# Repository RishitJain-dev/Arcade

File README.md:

# Arcade
A custom console similar to the Nintendo Game&amp;Watch, with a large colorful screen, d-pad and A and B button. It also includes a USB-C connector and SD card slot. 

Using SK8612-MINI-E LEDs to provide as a visual indicator of when a button is pressed

It uses a ESP32 chip to power it and recieves power directly from a LiPo battery.

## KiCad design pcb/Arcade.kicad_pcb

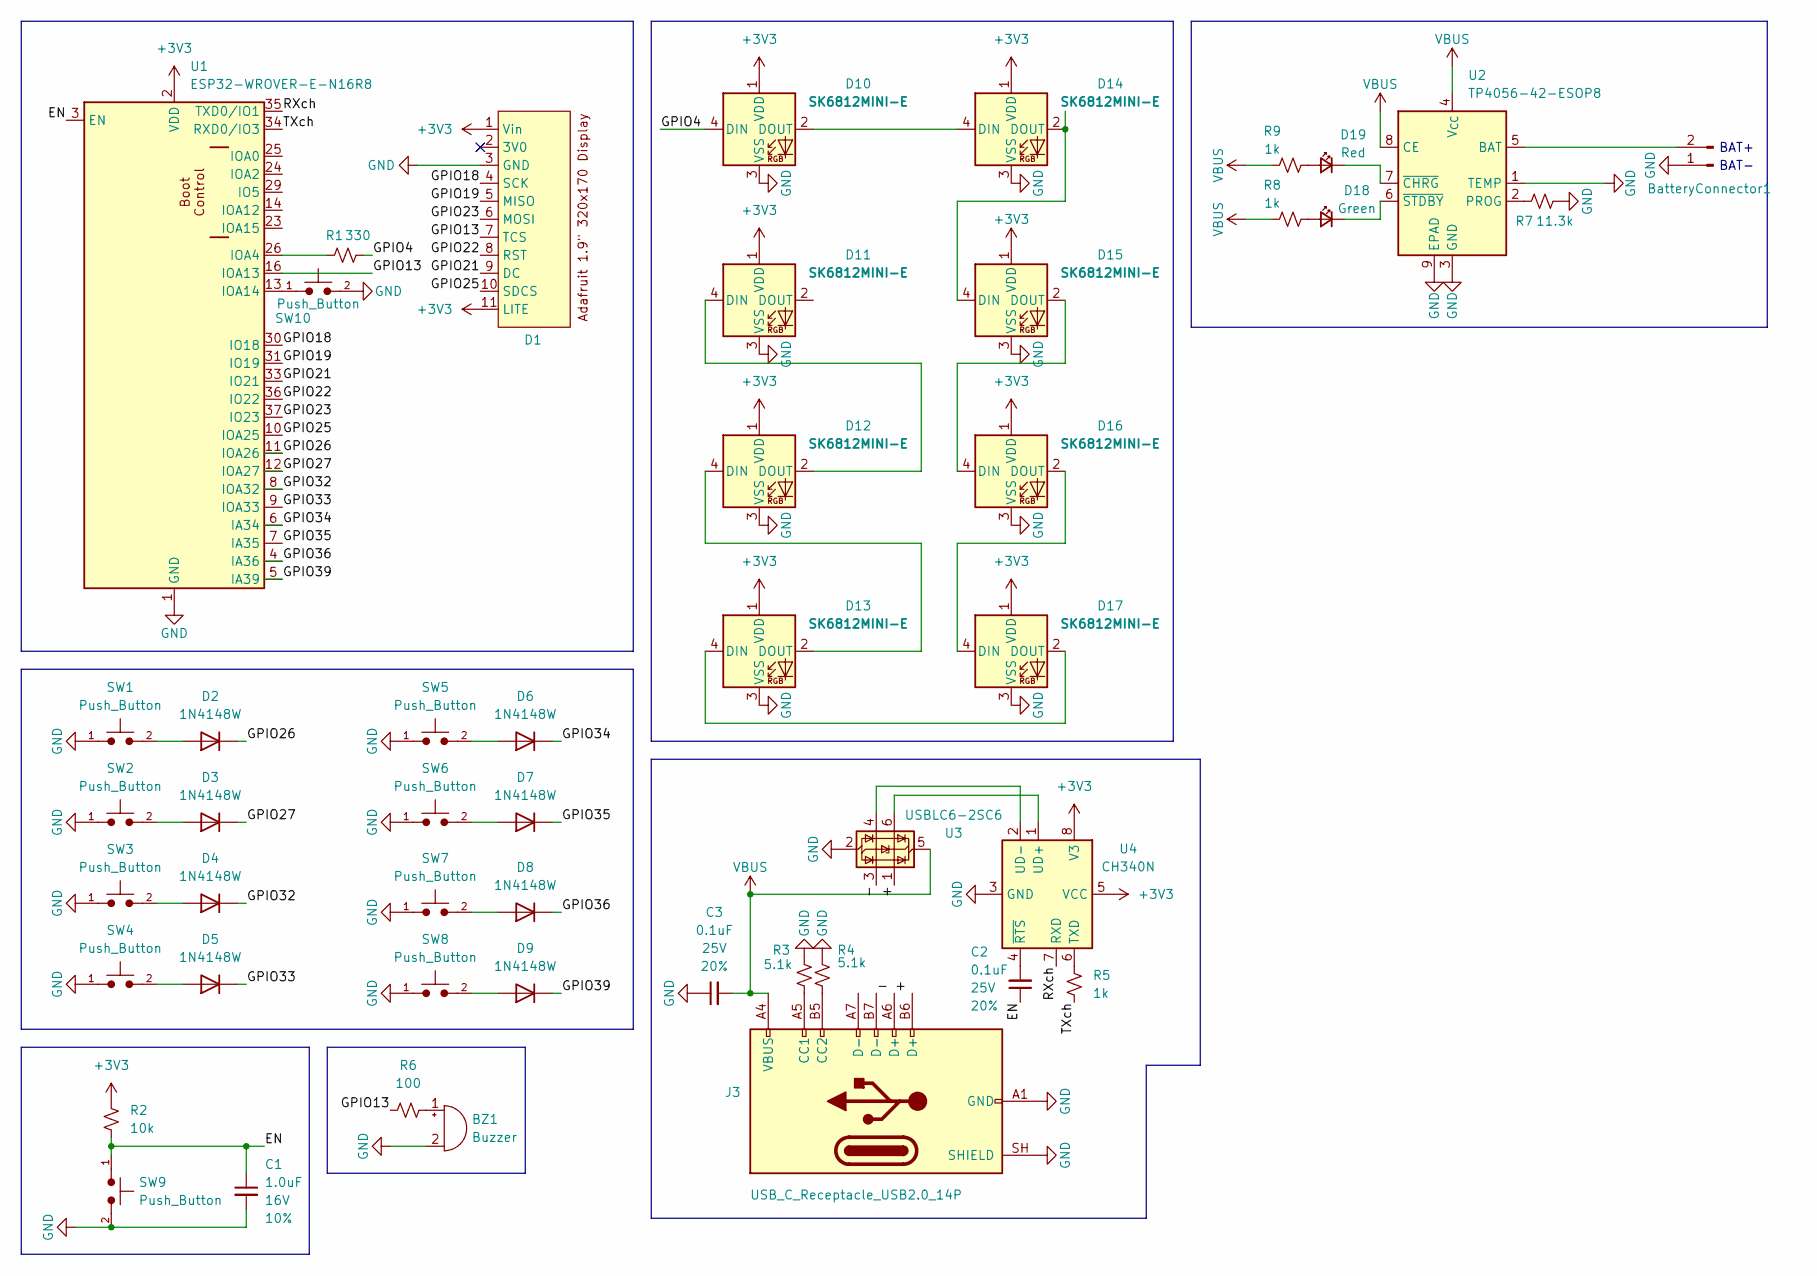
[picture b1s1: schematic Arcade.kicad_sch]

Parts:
BZ1: Buzzer; Buzzer_12x9.5RM7.6
BatteryConnector1: BAT-; JST_EH_B2B-EH-A_1x02_P2.50mm_Vertical
C1: 1.0uF; C_0603_1608Metric; Voltage 16V; Tolerance 10%
C2, C3: 0.1uF; C_0603_1608Metric; Voltage 25V; Tolerance 20%
D1: Adafruit 1.9 320x170 Colour IPS TFT Display (ST7789)
D2, D3, D4, D5, D6, D7, D8, D9: 1N4148W; D_SOD-123
D10, D11, D12, D13, D14, D15, D16, D17: SK6812MINI-E; LED_SK6812MINI-E_3.2x2.8mm_P1.5mm_ReverseMount
D18: Green; LED_0603_1608Metric_Green
D19: Red; LED_0603_1608Metric_Red
J3: USB_C_Receptacle_USB2.0_14P; USB_C_Receptacle_HRO_TYPE-C-31-M-12
R1: 330; R_0603_1608Metric
R2: 10k; R_0603_1608Metric
R3, R4: 5.1k; R_0603_1608Metric
R5, R8, R9: 1k; R_0603_1608Metric
R6: 100; R_0603_1608Metric
R7: 11.3k; R_0603_1608Metric
SW1, SW2, SW3, SW4, SW5, SW6, SW7, SW8, SW9, SW10: Push_Button; SW_PUSH_6mm
U1: ESP32-WROVER-E-N16R8; ESP32-WROVER-E-IE
U2: TP4056-42-ESOP8; SOIC-8-1EP_3.9x4.9mm_P1.27mm_EP2.41x3.3mm_ThermalVias
U3: USBLC6-2SC6; SOT-23-6
U4: CH340N; JEITA_SOIC-8_3.9x4.9mm_P1.27mm

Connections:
+3V3: D1.1 (Vin), D1.11 (LITE), D10.1 (VDD), D11.1 (VDD), D12.1 (VDD), D13.1 (VDD), D14.1 (VDD), D15.1 (VDD), D16.1 (VDD), D17.1 (VDD), R2.2, U1.2 (VDD), U4.5 (VCC), U4.8 (V3)
/+: J3.A6 (D+), U3.1 (I/O1)
/-: J3.B7 (D-), U3.3 (I/O2)
/EN: C1.1, C2.1, R2.1, SW9.1, U1.3 (EN)
/GPIO4: D10.4 (DIN), R1.2
/GPIO13: D1.7 (TCS), R6.1, U1.16 (IOA13)
/GPIO18: D1.4 (SCK), U1.30 (IO18)
/GPIO19: D1.5 (MISO), U1.31 (IO19)
/GPIO21: D1.9 (DC), U1.33 (IO21)
/GPIO22: D1.8 (RST), U1.36 (IO22)
/GPIO23: D1.6 (MOSI), U1.37 (IO23)
/GPIO25: D1.10 (SDCS), U1.10 (IOA25)
/GPIO26: D2.1 (K), U1.11 (IOA26)
/GPIO27: D3.1 (K), U1.12 (IOA27)
/GPIO32: D4.1 (K), U1.8 (IOA32)
/GPIO33: D5.1 (K), U1.9 (IOA33)
/GPIO34: D6.1 (K), U1.6 (IA34)
/GPIO35: D7.1 (K), U1.7 (IA35)
/GPIO36: D8.1 (K), U1.4 (IA36)
/GPIO39: D9.1 (K), U1.5 (IA39)
/RXch: U1.35 (TXD0/IO1), U4.7 (RXD)
/TXch: R5.1, U1.34 (RXD0/IO3)
GND: BZ1.2 (-), BatteryConnector1.1, C1.2, C3.1, D1.3 (GND), D10.3 (VSS), D11.3 (VSS), D12.3 (VSS), D13.3 (VSS), D14.3 (VSS), D15.3 (VSS), D16.3 (VSS), D17.3 (VSS), J3.A1 (GND), J3.A12 (GND), J3.B1 (GND), J3.B12 (GND), J3.SH (SHIELD), R3.2, R4.2, R7.2, SW1.1, SW2.1, SW3.1, SW4.1, SW5.1, SW6.1, SW7.1, SW8.1, SW9.2, SW10.2, U1.1 (GND), U1.15 (GND), U1.38 (GND), U1.39.1 (GND), U1.39.2 (GND), U1.39.3 (GND), U1.39.4 (GND), U1.39.5 (GND), U1.39.6 (GND), U1.39.7 (GND), U1.39.8 (GND), U1.39.9 (GND), U2.1 (TEMP), U2.3 (GND), U2.9 (EPAD), U3.2 (GND), U4.3 (GND)
unnamed: BZ1.1 (+), R6.2
unnamed: BatteryConnector1.2, U2.5 (BAT)
unnamed: D2.2 (A), SW1.2
unnamed: D3.2 (A), SW2.2
unnamed: D4.2 (A), SW3.2
unnamed: D5.2 (A), SW4.2
unnamed: D6.2 (A), SW5.2
unnamed: D7.2 (A), SW6.2
unnamed: D8.2 (A), SW7.2
unnamed: D9.2 (A), SW8.2
unnamed: D10.2 (DOUT), D14.4 (DIN)
unnamed: D11.4 (DIN), D12.2 (DOUT)
unnamed: D12.4 (DIN), D13.2 (DOUT)
unnamed: D13.4 (DIN), D17.2 (DOUT)
unnamed: D14.2 (DOUT), D15.4 (DIN)
unnamed: D15.2 (DOUT), D16.4 (DIN)
unnamed: D16.2 (DOUT), D17.4 (DIN)
unnamed: D18.2 (A), R8.2
unnamed: D18.1 (K), U2.6 (~STDBY)
unnamed: D19.2 (A), R9.2
unnamed: D19.1 (K), U2.7 (~CHRG)
unnamed: J3.A5 (CC1), R3.1
unnamed: J3.B5 (CC2), R4.1
unnamed: R1.1, U1.26 (IOA4)
unnamed: SW10.1, U1.13 (IOA14)
unnamed: R7.1, U2.2 (PROG)
unnamed: R5.2, U4.6 (TXD)
unnamed: U3.6 (I/O1), U4.1 (UD+)
unnamed: U3.4 (I/O2), U4.2 (UD-)
unnamed: C2.2, U4.4 (~RTS)
VBUS: C3.2, J3.A4 (VBUS), J3.A9 (VBUS), J3.B4 (VBUS), J3.B9 (VBUS), R8.1, R9.1, U2.4 (V_{CC}), U2.8 (CE), U3.5 (VBUS)

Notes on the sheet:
BAT+
BAT-

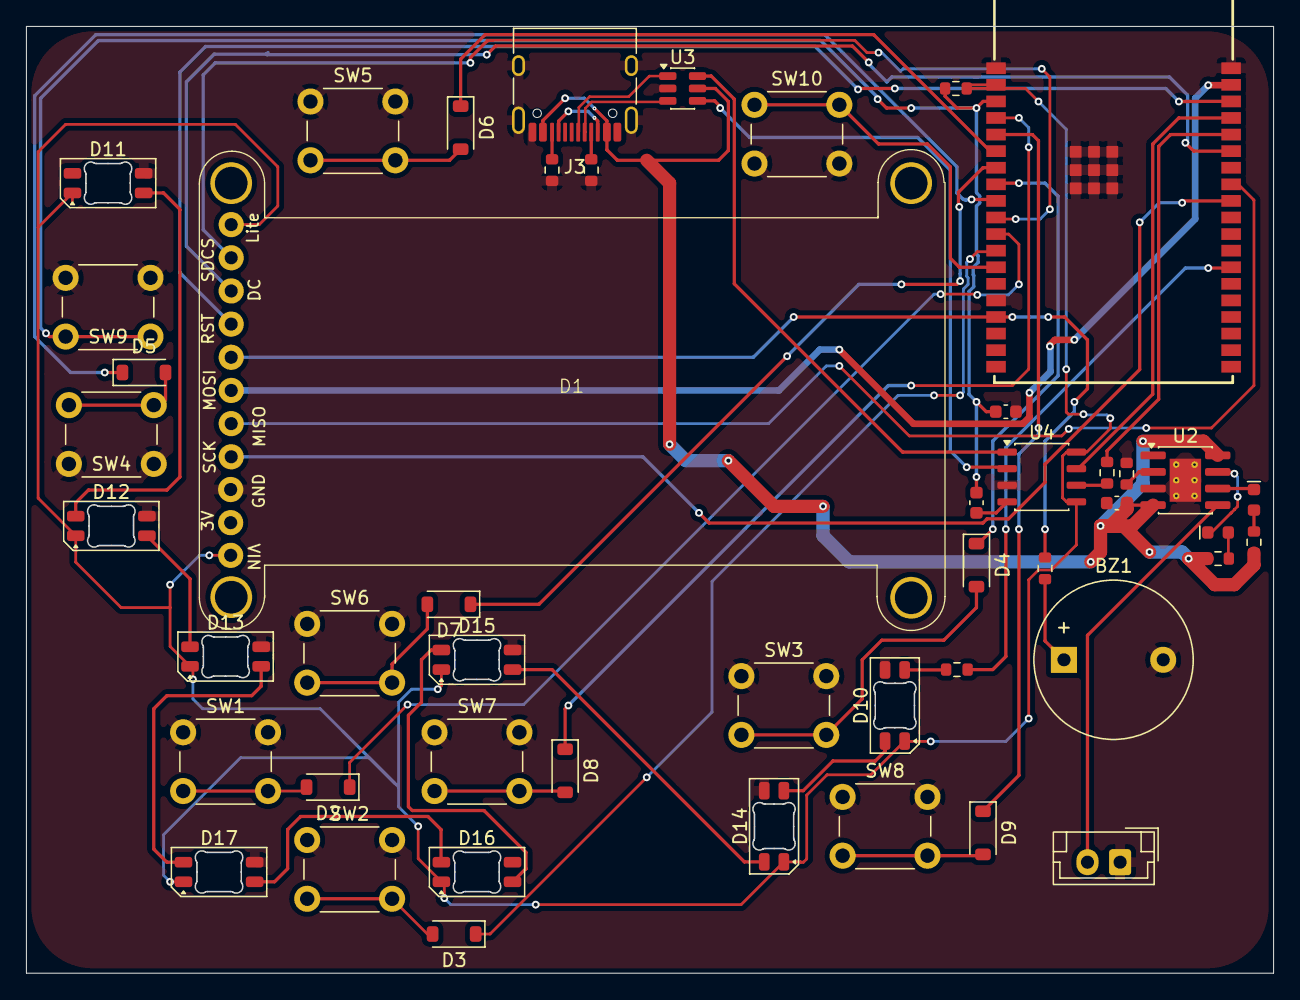
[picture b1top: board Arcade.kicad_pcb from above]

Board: 2 copper layers, 95.5 x 72.5 mm, 48 parts (0 on the bottom side), 54 nets.
